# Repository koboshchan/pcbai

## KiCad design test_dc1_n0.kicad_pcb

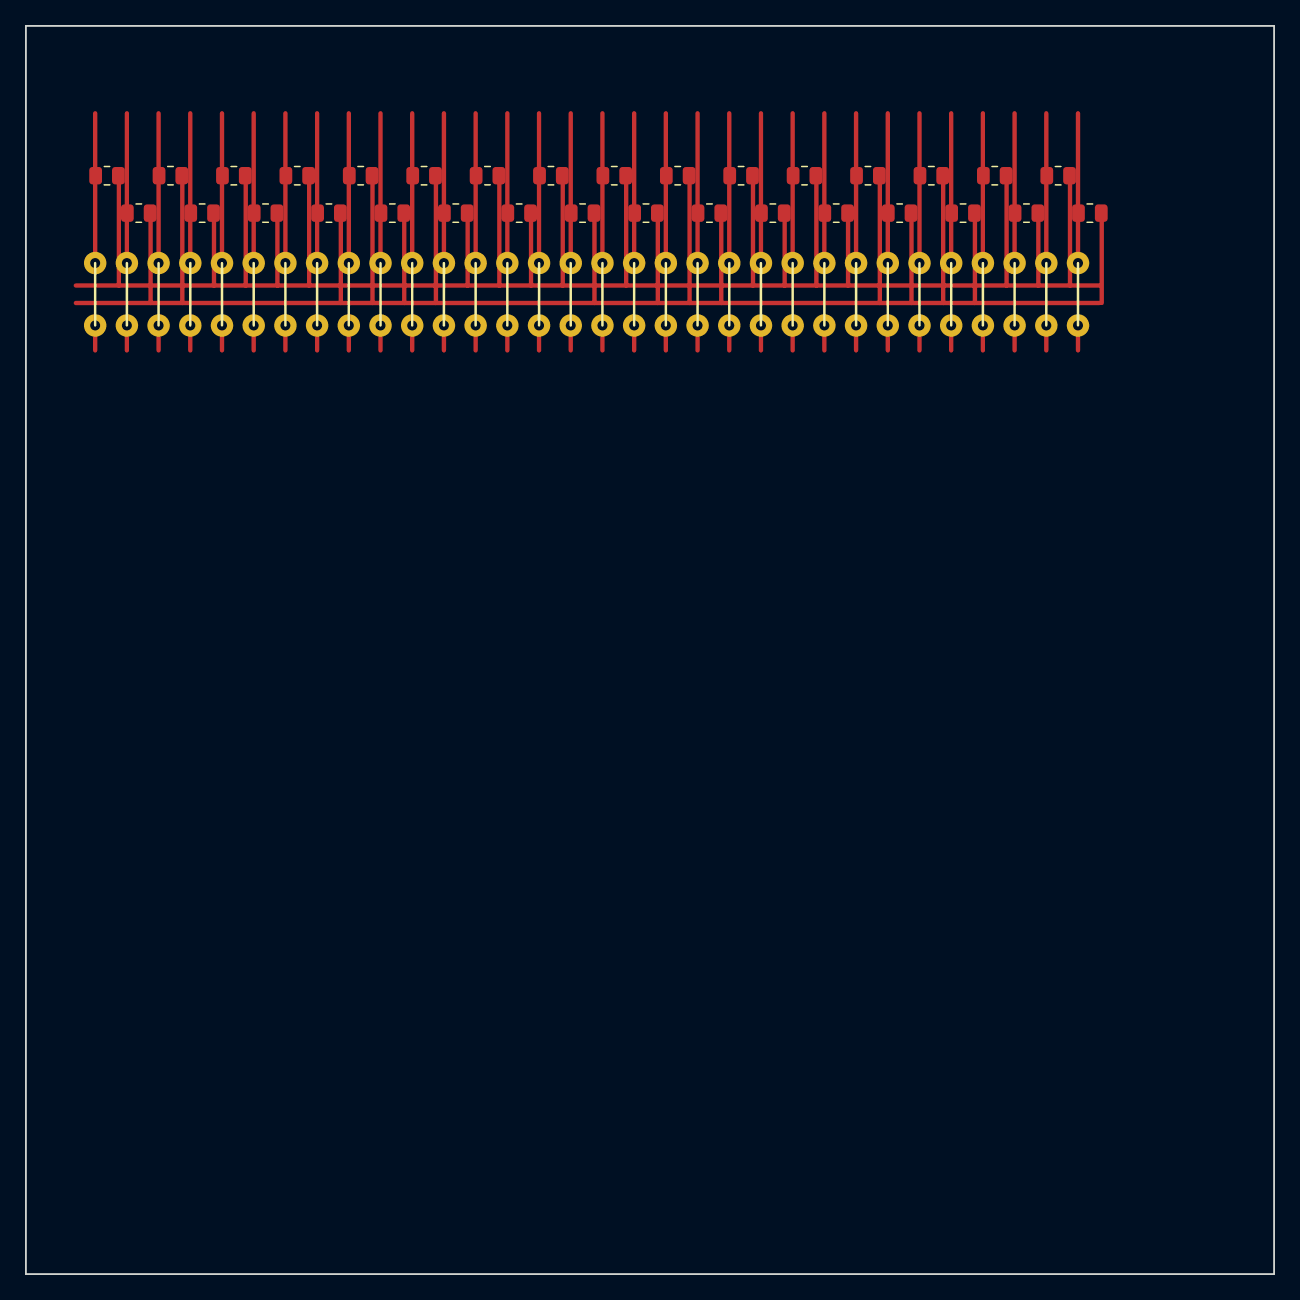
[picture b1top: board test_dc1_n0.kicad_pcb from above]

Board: 2 copper layers, 100.0 x 100.0 mm, 64 parts (0 on the bottom side), 34 nets.

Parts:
R1_0_0, R1_4_0, R1_7_0, R1_21_0, R1_22_0, R1_27_0: 12k; R_0805_2012Metric
R1_1_0, R1_10_0, R1_28_0: 200k; R_0805_2012Metric
R1_2_0, R1_8_0, R1_16_0, R1_24_0, R1_29_0: 22k; R_0805_2012Metric
R1_3_0: 100k; R_0805_2012Metric
R1_5_0, R1_9_0, R1_13_0, R1_14_0, R1_25_0, R1_26_0: 33k; R_0805_2012Metric
R1_6_0, R1_11_0, R1_17_0: 75k; R_0805_2012Metric
R1_12_0: 18k; R_0805_2012Metric
R1_15_0: 300k; R_0805_2012Metric
R1_18_0: 43k; R_0805_2012Metric
R1_19_0: 10k; R_0805_2012Metric
R1_20_0: 51k; R_0805_2012Metric
R1_23_0: 15k; R_0805_2012Metric
R1_30_0: 20k; R_0805_2012Metric
R1_31_0: 390k; R_0805_2012Metric
W1, W2, W3, W4, W5, W6, W7, W8, W9, W10, W11, W12, W13, W14, W15, W16, W17, W18, W19, W20, W21, W22, W23, W24, W25, W26, W27, W28, W29, W30, W31, W32: JUMPER; Jumper_Wire

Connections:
IN_0: R1_0_0.1, W1.1
IN_1: R1_1_0.1, W2.1
IN_2: R1_2_0.1, W3.1
IN_3: R1_3_0.1, W4.1
IN_4: R1_4_0.1, W5.1
IN_5: R1_5_0.1, W6.1
IN_6: R1_6_0.1, W7.1
IN_7: R1_7_0.1, W8.1
IN_8: R1_8_0.1, W9.1
IN_9: R1_9_0.1, W10.1
IN_10: R1_10_0.1, W11.1
IN_11: R1_11_0.1, W12.1
IN_12: R1_12_0.1, W13.1
IN_13: R1_13_0.1, W14.1
IN_14: R1_14_0.1, W15.1
IN_15: R1_15_0.1, W16.1
IN_16: R1_16_0.1, W17.1
IN_17: R1_17_0.1, W18.1
IN_18: R1_18_0.1, W19.1
IN_19: R1_19_0.1, W20.1
IN_20: R1_20_0.1, W21.1
IN_21: R1_21_0.1, W22.1
IN_22: R1_22_0.1, W23.1
IN_23: R1_23_0.1, W24.1
IN_24: R1_24_0.1, W25.1
IN_25: R1_25_0.1, W26.1
IN_26: R1_26_0.1, W27.1
IN_27: R1_27_0.1, W28.1
IN_28: R1_28_0.1, W29.1
IN_29: R1_29_0.1, W30.1
IN_30: R1_30_0.1, W31.1
IN_31: R1_31_0.1, W32.1
SUM_NEG_0: R1_1_0.2, R1_2_0.2, R1_7_0.2, R1_8_0.2, R1_9_0.2, R1_10_0.2, R1_15_0.2, R1_17_0.2, R1_18_0.2, R1_19_0.2, R1_24_0.2, R1_25_0.2, R1_26_0.2, R1_27_0.2, R1_31_0.2
SUM_POS_0: R1_0_0.2, R1_3_0.2, R1_4_0.2, R1_5_0.2, R1_6_0.2, R1_11_0.2, R1_12_0.2, R1_13_0.2, R1_14_0.2, R1_16_0.2, R1_20_0.2, R1_21_0.2, R1_22_0.2, R1_23_0.2, R1_28_0.2, R1_29_0.2, R1_30_0.2

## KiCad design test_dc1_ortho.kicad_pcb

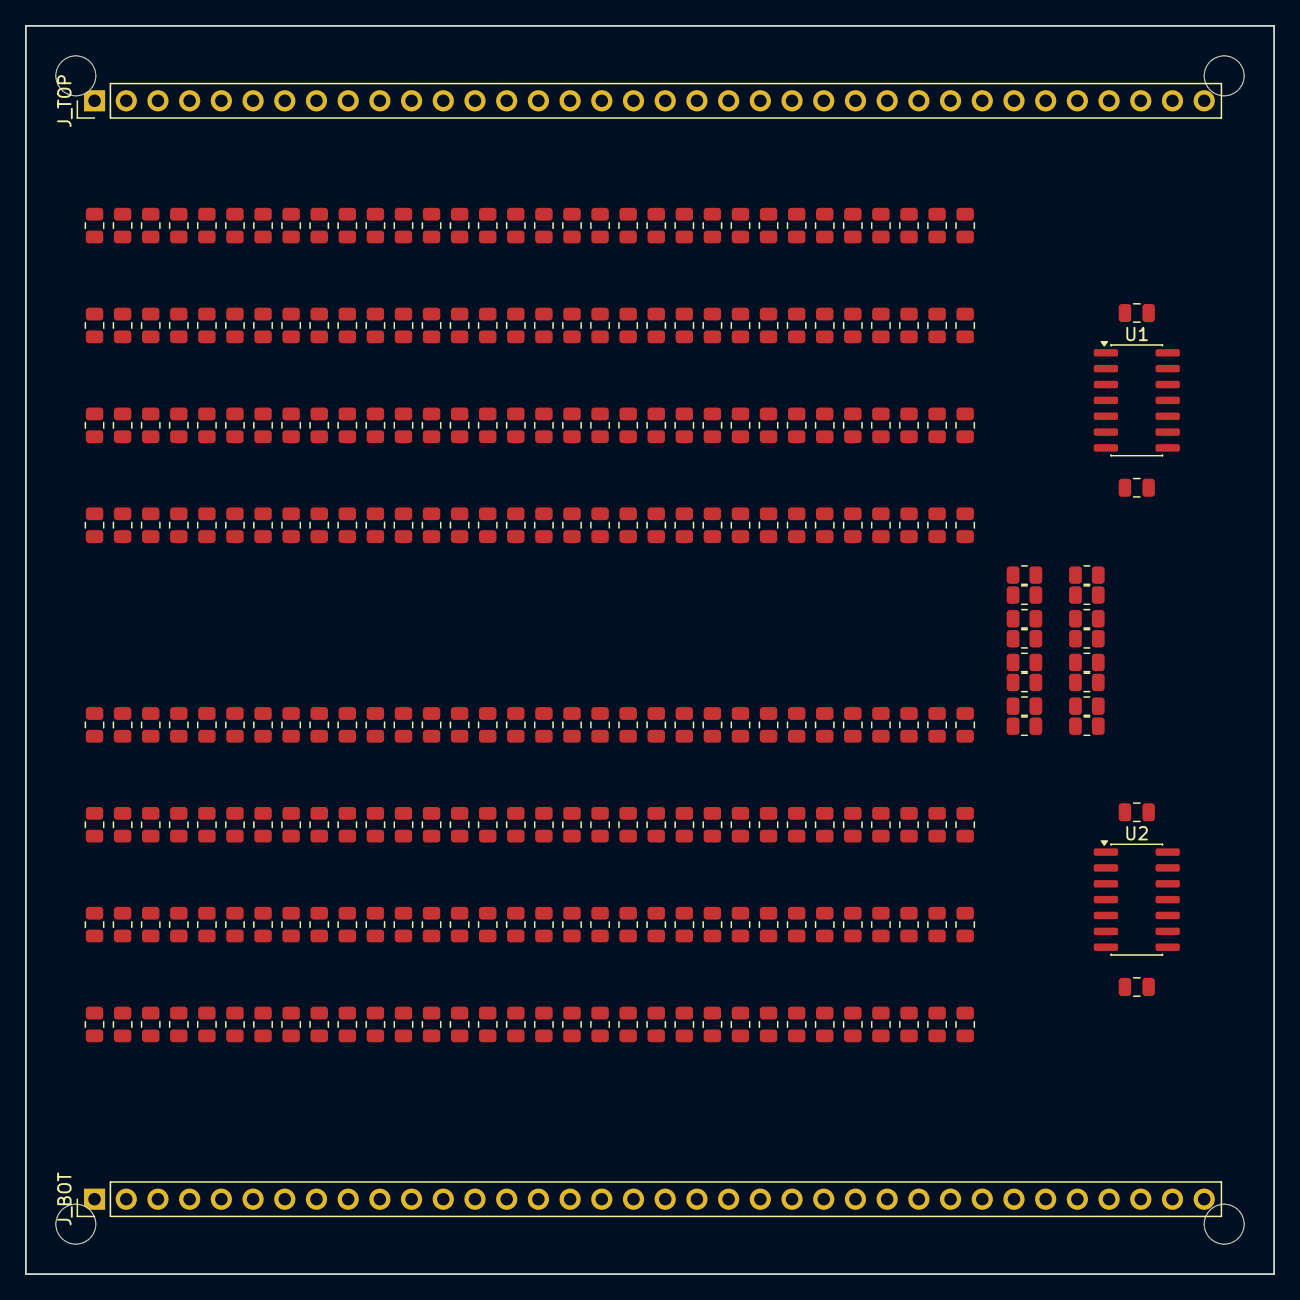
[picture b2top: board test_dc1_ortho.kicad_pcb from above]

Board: 2 copper layers, 100.0 x 100.0 mm, 284 parts (0 on the bottom side), 84 nets, no tracks yet.

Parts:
C_U1_NEG, C_U1_POS, C_U2_NEG, C_U2_POS: 100n; C_0805_2012Metric
J_BOT: INPUTS_32_63_SUM; PinHeader_1x36_P2.54mm_Vertical
J_TOP: INPUTS_0_31_PWR; PinHeader_1x36_P2.54mm_Vertical
MH1, MH2, MH3, MH4: MountingHole_3.2mm_M3
R1_0_0, R1_4_0, R1_7_0, R1_21_0, R1_22_0, R1_26_3, R1_27_0, R1_40_3, R1_55_0, R1_62_0, R1_63_3: 12k; R_0805_2012Metric
R1_0_1, R1_3_3, R1_6_1, R1_13_1, R1_14_1, R1_15_0, R1_25_1, R1_27_1, R1_48_1, R1_50_3: 300k; R_0805_2012Metric
R1_0_2, R1_6_3, R1_11_1, R1_12_1, R1_20_0, R1_30_1, R1_34_2, R1_38_0, R1_38_2, R1_40_0, R1_44_1, R1_45_0, R1_45_1, R1_46_2, R1_49_1, R1_50_1, R1_53_1, R1_53_3, R1_59_1, R1_60_1, R1_62_2: 51k; R_0805_2012Metric
R1_0_3, R1_3_2, R1_11_3, R1_13_2, R1_18_0, R1_27_2, R1_35_2, R1_37_0, R1_48_2, R1_49_0, R1_57_2, R1_60_0: 43k; R_0805_2012Metric
R1_1_0, R1_1_2, R1_7_1, R1_10_0, R1_10_2, R1_16_1, R1_18_1, R1_19_1, R1_20_3, R1_21_3, R1_24_1, R1_28_0, R1_28_3, R1_31_1, R1_33_1, R1_34_1, R1_35_0, R1_36_3, R1_37_1, R1_39_2, R1_39_3, R1_44_2, R1_44_3, R1_46_1, R1_50_0, R1_51_2, R1_52_1, R1_52_3, R1_53_2, R1_54_3, R1_57_0, R1_58_0, R1_58_3, R1_59_0, R1_62_1: 200k; R_0805_2012Metric
R1_1_1, R1_5_3, R1_26_1, R1_31_0, R1_46_3, R1_47_1, R1_48_0: 390k; R_0805_2012Metric
R1_1_3, R1_4_1, R1_5_1, R1_6_0, R1_8_1, R1_10_1, R1_11_0, R1_17_0, R1_22_3, R1_29_3, R1_30_2, R1_32_0, R1_32_1, R1_32_2, R1_35_1, R1_36_2, R1_37_2, R1_42_3, R1_43_0, R1_44_0, R1_46_0, R1_48_3, R1_50_2, R1_51_1, R1_51_3, R1_52_2, R1_53_0, R1_54_1, R1_57_1, R1_59_2, R1_61_2, R1_62_3: 75k; R_0805_2012Metric
R1_2_0, R1_2_2, R1_8_0, R1_8_2, R1_14_2, R1_16_0, R1_18_2, R1_23_3, R1_24_0, R1_26_2, R1_29_0, R1_36_0, R1_38_3, R1_41_3, R1_42_2, R1_43_2, R1_47_3, R1_49_3, R1_54_0, R1_54_2, R1_55_2, R1_55_3, R1_59_3: 22k; R_0805_2012Metric
R1_2_1, R1_2_3, R1_3_0, R1_3_1, R1_9_1, R1_11_2, R1_12_2, R1_12_3, R1_14_3, R1_15_1, R1_17_1, R1_21_1, R1_23_1, R1_28_2, R1_31_3, R1_33_0, R1_33_2, R1_36_1, R1_38_1, R1_39_1, R1_41_1, R1_42_1, R1_43_1, R1_45_3, R1_51_0, R1_52_0, R1_55_1, R1_58_1, R1_58_2, R1_60_2, R1_61_1, R1_63_1: 100k; R_0805_2012Metric
R1_4_2, R1_4_3, R1_5_0, R1_5_2, R1_9_0, R1_9_3, R1_10_3, R1_13_0, R1_14_0, R1_16_2, R1_17_2, R1_19_2, R1_24_2, R1_25_0, R1_26_0, R1_27_3, R1_30_3, R1_33_3, R1_34_0, R1_37_3, R1_40_2, R1_41_2, R1_42_0, R1_43_3, R1_47_0, R1_49_2, R1_56_3, R1_57_3, R1_63_2: 33k; R_0805_2012Metric
R1_6_2, R1_61_0, R1_63_0: 680k; R_0805_2012Metric
R1_7_2, R1_15_2, R1_17_3, R1_19_0, R1_21_2, R1_25_3, R1_56_0: 10k; R_0805_2012Metric
R1_7_3, R1_9_2, R1_19_3, R1_20_2, R1_30_0, R1_41_0: 20k; R_0805_2012Metric
R1_8_3, R1_12_0, R1_35_3: 18k; R_0805_2012Metric
R1_13_3, R1_20_1, R1_22_1, R1_28_1, R1_29_1, R1_40_1, R1_61_3: 1M; R_0805_2012Metric
R1_15_3, R1_18_3, R1_23_0, R1_29_2: 15k; R_0805_2012Metric
R1_16_3, R1_22_2, R1_23_2, R1_24_3, R1_31_2, R1_39_0: 7.5k; R_0805_2012Metric
R1_25_2, R1_45_2, R1_47_2, R1_60_3: 47k; R_0805_2012Metric
R1_32_3: 5.6k; R_0805_2012Metric
R1_34_3, R1_56_2: 470k; R_0805_2012Metric
R1_56_1: DNP; R_0805_2012Metric
Rb_N0: 390k; R_0805_2012Metric
Rb_N1: 470k; R_0805_2012Metric
Rb_N2, Rb_N3: 200k; R_0805_2012Metric
Rc_N0, Rc_N1, Rc_N2, Rc_N3: 10k; R_0805_2012Metric
Rf1_N0, Rf1_N1, Rf1_N2, Rf1_N3, Rf2_N0, Rf2_N1, Rf2_N2, Rf2_N3: 10k; R_0805_2012Metric
U1: TL074_INV; SOIC-14_3.9x8.7mm_P1.27mm
U2: TL074_SUM; SOIC-14_3.9x8.7mm_P1.27mm

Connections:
+5V_REF: J_TOP.36, Rb_N0.1, Rb_N1.1, Rb_N2.1, Rb_N3.1
+12V: C_U1_POS.1, C_U2_POS.1, J_TOP.33, U1.4, U2.4
-12V: C_U1_NEG.1, C_U2_NEG.1, J_TOP.34, U1.11, U2.11
GND: C_U1_NEG.2, C_U1_POS.2, C_U2_NEG.2, C_U2_POS.2, J_TOP.35, U1.3, U1.5, U1.10, U1.12, U2.3, U2.5, U2.10, U2.12
IN_0: J_TOP.1, R1_0_0.1, R1_0_1.1, R1_0_2.1, R1_0_3.1
IN_1: J_TOP.2, R1_1_0.1, R1_1_1.1, R1_1_2.1, R1_1_3.1
IN_2: J_TOP.3, R1_2_0.1, R1_2_1.1, R1_2_2.1, R1_2_3.1
IN_3: J_TOP.4, R1_3_0.1, R1_3_1.1, R1_3_2.1, R1_3_3.1
IN_4: J_TOP.5, R1_4_0.1, R1_4_1.1, R1_4_2.1, R1_4_3.1
IN_5: J_TOP.6, R1_5_0.1, R1_5_1.1, R1_5_2.1, R1_5_3.1
IN_6: J_TOP.7, R1_6_0.1, R1_6_1.1, R1_6_2.1, R1_6_3.1
IN_7: J_TOP.8, R1_7_0.1, R1_7_1.1, R1_7_2.1, R1_7_3.1
IN_8: J_TOP.9, R1_8_0.1, R1_8_1.1, R1_8_2.1, R1_8_3.1
IN_9: J_TOP.10, R1_9_0.1, R1_9_1.1, R1_9_2.1, R1_9_3.1
IN_10: J_TOP.11, R1_10_0.1, R1_10_1.1, R1_10_2.1, R1_10_3.1
IN_11: J_TOP.12, R1_11_0.1, R1_11_1.1, R1_11_2.1, R1_11_3.1
IN_12: J_TOP.13, R1_12_0.1, R1_12_1.1, R1_12_2.1, R1_12_3.1
IN_13: J_TOP.14, R1_13_0.1, R1_13_1.1, R1_13_2.1, R1_13_3.1
IN_14: J_TOP.15, R1_14_0.1, R1_14_1.1, R1_14_2.1, R1_14_3.1
IN_15: J_TOP.16, R1_15_0.1, R1_15_1.1, R1_15_2.1, R1_15_3.1
IN_16: J_TOP.17, R1_16_0.1, R1_16_1.1, R1_16_2.1, R1_16_3.1
IN_17: J_TOP.18, R1_17_0.1, R1_17_1.1, R1_17_2.1, R1_17_3.1
IN_18: J_TOP.19, R1_18_0.1, R1_18_1.1, R1_18_2.1, R1_18_3.1
IN_19: J_TOP.20, R1_19_0.1, R1_19_1.1, R1_19_2.1, R1_19_3.1
IN_20: J_TOP.21, R1_20_0.1, R1_20_1.1, R1_20_2.1, R1_20_3.1
IN_21: J_TOP.22, R1_21_0.1, R1_21_1.1, R1_21_2.1, R1_21_3.1
IN_22: J_TOP.23, R1_22_0.1, R1_22_1.1, R1_22_2.1, R1_22_3.1
IN_23: J_TOP.24, R1_23_0.1, R1_23_1.1, R1_23_2.1, R1_23_3.1
IN_24: J_TOP.25, R1_24_0.1, R1_24_1.1, R1_24_2.1, R1_24_3.1
IN_25: J_TOP.26, R1_25_0.1, R1_25_1.1, R1_25_2.1, R1_25_3.1
IN_26: J_TOP.27, R1_26_0.1, R1_26_1.1, R1_26_2.1, R1_26_3.1
IN_27: J_TOP.28, R1_27_0.1, R1_27_1.1, R1_27_2.1, R1_27_3.1
IN_28: J_TOP.29, R1_28_0.1, R1_28_1.1, R1_28_2.1, R1_28_3.1
IN_29: J_TOP.30, R1_29_0.1, R1_29_1.1, R1_29_2.1, R1_29_3.1
IN_30: J_TOP.31, R1_30_0.1, R1_30_1.1, R1_30_2.1, R1_30_3.1
IN_31: J_TOP.32, R1_31_0.1, R1_31_1.1, R1_31_2.1, R1_31_3.1
IN_32: J_BOT.1, R1_32_0.1, R1_32_1.1, R1_32_2.1, R1_32_3.1
IN_33: J_BOT.2, R1_33_0.1, R1_33_1.1, R1_33_2.1, R1_33_3.1
IN_34: J_BOT.3, R1_34_0.1, R1_34_1.1, R1_34_2.1, R1_34_3.1
IN_35: J_BOT.4, R1_35_0.1, R1_35_1.1, R1_35_2.1, R1_35_3.1
IN_36: J_BOT.5, R1_36_0.1, R1_36_1.1, R1_36_2.1, R1_36_3.1
IN_37: J_BOT.6, R1_37_0.1, R1_37_1.1, R1_37_2.1, R1_37_3.1
IN_38: J_BOT.7, R1_38_0.1, R1_38_1.1, R1_38_2.1, R1_38_3.1
IN_39: J_BOT.8, R1_39_0.1, R1_39_1.1, R1_39_2.1, R1_39_3.1
IN_40: J_BOT.9, R1_40_0.1, R1_40_1.1, R1_40_2.1, R1_40_3.1
IN_41: J_BOT.10, R1_41_0.1, R1_41_1.1, R1_41_2.1, R1_41_3.1
IN_42: J_BOT.11, R1_42_0.1, R1_42_1.1, R1_42_2.1, R1_42_3.1
IN_43: J_BOT.12, R1_43_0.1, R1_43_1.1, R1_43_2.1, R1_43_3.1
IN_44: J_BOT.13, R1_44_0.1, R1_44_1.1, R1_44_2.1, R1_44_3.1
IN_45: J_BOT.14, R1_45_0.1, R1_45_1.1, R1_45_2.1, R1_45_3.1
IN_46: J_BOT.15, R1_46_0.1, R1_46_1.1, R1_46_2.1, R1_46_3.1
IN_47: J_BOT.16, R1_47_0.1, R1_47_1.1, R1_47_2.1, R1_47_3.1
IN_48: J_BOT.17, R1_48_0.1, R1_48_1.1, R1_48_2.1, R1_48_3.1
IN_49: J_BOT.18, R1_49_0.1, R1_49_1.1, R1_49_2.1, R1_49_3.1
IN_50: J_BOT.19, R1_50_0.1, R1_50_1.1, R1_50_2.1, R1_50_3.1
IN_51: J_BOT.20, R1_51_0.1, R1_51_1.1, R1_51_2.1, R1_51_3.1
IN_52: J_BOT.21, R1_52_0.1, R1_52_1.1, R1_52_2.1, R1_52_3.1
IN_53: J_BOT.22, R1_53_0.1, R1_53_1.1, R1_53_2.1, R1_53_3.1
IN_54: J_BOT.23, R1_54_0.1, R1_54_1.1, R1_54_2.1, R1_54_3.1
IN_55: J_BOT.24, R1_55_0.1, R1_55_1.1, R1_55_2.1, R1_55_3.1
IN_56: J_BOT.25, R1_56_0.1, R1_56_1.1, R1_56_2.1, R1_56_3.1
IN_57: J_BOT.26, R1_57_0.1, R1_57_1.1, R1_57_2.1, R1_57_3.1
IN_58: J_BOT.27, R1_58_0.1, R1_58_1.1, R1_58_2.1, R1_58_3.1
IN_59: J_BOT.28, R1_59_0.1, R1_59_1.1, R1_59_2.1, R1_59_3.1
IN_60: J_BOT.29, R1_60_0.1, R1_60_1.1, R1_60_2.1, R1_60_3.1
IN_61: J_BOT.30, R1_61_0.1, R1_61_1.1, R1_61_2.1, R1_61_3.1
IN_62: J_BOT.31, R1_62_0.1, R1_62_1.1, R1_62_2.1, R1_62_3.1
IN_63: J_BOT.32, R1_63_0.1, R1_63_1.1, R1_63_2.1, R1_63_3.1
SUM_NEG_0: R1_1_0.2, R1_2_0.2, R1_7_0.2, R1_8_0.2, R1_9_0.2, R1_10_0.2, R1_15_0.2, R1_17_0.2, R1_18_0.2, R1_19_0.2, R1_24_0.2, R1_25_0.2, R1_26_0.2, R1_27_0.2, R1_31_0.2, R1_33_0.2, R1_34_0.2, R1_35_0.2, R1_38_0.2, R1_39_0.2, R1_40_0.2, R1_41_0.2, R1_42_0.2, R1_46_0.2, R1_47_0.2, R1_48_0.2, R1_49_0.2, R1_50_0.2, R1_51_0.2, R1_52_0.2, R1_58_0.2, R1_59_0.2, R1_60_0.2, R1_61_0.2, R1_63_0.2, Rf1_N0.2, U1.2
SUM_NEG_1: R1_1_1.2, R1_3_1.2, R1_4_1.2, R1_5_1.2, R1_9_1.2, R1_10_1.2, R1_11_1.2, R1_12_1.2, R1_13_1.2, R1_14_1.2, R1_16_1.2, R1_17_1.2, R1_19_1.2, R1_20_1.2, R1_21_1.2, R1_22_1.2, R1_23_1.2, R1_24_1.2, R1_27_1.2, R1_28_1.2, R1_30_1.2, R1_31_1.2, R1_33_1.2, R1_34_1.2, R1_35_1.2, R1_36_1.2, R1_37_1.2, R1_38_1.2, R1_39_1.2, R1_41_1.2, R1_42_1.2, R1_43_1.2, R1_44_1.2, R1_45_1.2, R1_49_1.2, R1_50_1.2, R1_51_1.2, R1_52_1.2, R1_53_1.2, R1_54_1.2, R1_55_1.2, R1_57_1.2, R1_58_1.2, R1_59_1.2, R1_60_1.2, R1_61_1.2, R1_62_1.2, R1_63_1.2, Rb_N1.2, Rf1_N1.2, U1.6
SUM_NEG_2: R1_0_2.2, R1_1_2.2, R1_2_2.2, R1_5_2.2, R1_6_2.2, R1_8_2.2, R1_9_2.2, R1_10_2.2, R1_11_2.2, R1_12_2.2, R1_16_2.2, R1_28_2.2, R1_31_2.2, R1_32_2.2, R1_33_2.2, R1_34_2.2, R1_35_2.2, R1_36_2.2, R1_38_2.2, R1_41_2.2, R1_42_2.2, R1_43_2.2, R1_44_2.2, R1_49_2.2, R1_50_2.2, R1_52_2.2, R1_56_2.2, R1_57_2.2, R1_60_2.2, R1_62_2.2, R1_63_2.2, Rf1_N2.2, U1.9
SUM_NEG_3: R1_0_3.2, R1_3_3.2, R1_4_3.2, R1_5_3.2, R1_6_3.2, R1_20_3.2, R1_24_3.2, R1_25_3.2, R1_26_3.2, R1_27_3.2, R1_29_3.2, R1_30_3.2, R1_32_3.2, R1_33_3.2, R1_36_3.2, R1_37_3.2, R1_38_3.2, R1_44_3.2, R1_45_3.2, R1_46_3.2, R1_50_3.2, R1_51_3.2, R1_56_3.2, R1_57_3.2, R1_58_3.2, R1_59_3.2, R1_60_3.2, R1_62_3.2, R1_63_3.2, Rb_N3.2, Rf1_N3.2, U1.13
SUM_POS_0: R1_0_0.2, R1_3_0.2, R1_4_0.2, R1_5_0.2, R1_6_0.2, R1_11_0.2, R1_12_0.2, R1_13_0.2, R1_14_0.2, R1_16_0.2, R1_20_0.2, R1_21_0.2, R1_22_0.2, R1_23_0.2, R1_28_0.2, R1_29_0.2, R1_30_0.2, R1_32_0.2, R1_36_0.2, R1_37_0.2, R1_43_0.2, R1_44_0.2, R1_45_0.2, R1_53_0.2, R1_54_0.2, R1_55_0.2, R1_56_0.2, R1_57_0.2, R1_62_0.2, Rb_N0.2, Rc_N0.2, Rf2_N0.2, U2.2
SUM_POS_1: R1_0_1.2, R1_2_1.2, R1_6_1.2, R1_7_1.2, R1_8_1.2, R1_15_1.2, R1_18_1.2, R1_25_1.2, R1_26_1.2, R1_29_1.2, R1_32_1.2, R1_40_1.2, R1_46_1.2, R1_47_1.2, R1_48_1.2, R1_56_1.2, Rc_N1.2, Rf2_N1.2, U2.6
SUM_POS_2: R1_3_2.2, R1_4_2.2, R1_7_2.2, R1_13_2.2, R1_14_2.2, R1_15_2.2, R1_17_2.2, R1_18_2.2, R1_19_2.2, R1_20_2.2, R1_21_2.2, R1_22_2.2, R1_23_2.2, R1_24_2.2, R1_25_2.2, R1_26_2.2, R1_27_2.2, R1_29_2.2, R1_30_2.2, R1_37_2.2, R1_39_2.2, R1_40_2.2, R1_45_2.2, R1_46_2.2, R1_47_2.2, R1_48_2.2, R1_51_2.2, R1_53_2.2, R1_54_2.2, R1_55_2.2, R1_58_2.2, R1_59_2.2, R1_61_2.2, Rb_N2.2, Rc_N2.2, Rf2_N2.2, U2.9
SUM_POS_3: R1_1_3.2, R1_2_3.2, R1_7_3.2, R1_8_3.2, R1_9_3.2, R1_10_3.2, R1_11_3.2, R1_12_3.2, R1_13_3.2, R1_14_3.2, R1_15_3.2, R1_16_3.2, R1_17_3.2, R1_18_3.2, R1_19_3.2, R1_21_3.2, R1_22_3.2, R1_23_3.2, R1_28_3.2, R1_31_3.2, R1_34_3.2, R1_35_3.2, R1_39_3.2, R1_40_3.2, R1_41_3.2, R1_42_3.2, R1_43_3.2, R1_47_3.2, R1_48_3.2, R1_49_3.2, R1_52_3.2, R1_53_3.2, R1_54_3.2, R1_55_3.2, R1_61_3.2, Rc_N3.2, Rf2_N3.2, U2.13
V_INV_0: Rc_N0.1, Rf1_N0.1, U1.1
V_INV_1: Rc_N1.1, Rf1_N1.1, U1.7
V_INV_2: Rc_N2.1, Rf1_N2.1, U1.8
V_INV_3: Rc_N3.1, Rf1_N3.1, U1.14
V_SUM_0: J_BOT.33, Rf2_N0.1, U2.1
V_SUM_1: J_BOT.34, Rf2_N1.1, U2.7
V_SUM_2: J_BOT.35, Rf2_N2.1, U2.8
V_SUM_3: J_BOT.36, Rf2_N3.1, U2.14
